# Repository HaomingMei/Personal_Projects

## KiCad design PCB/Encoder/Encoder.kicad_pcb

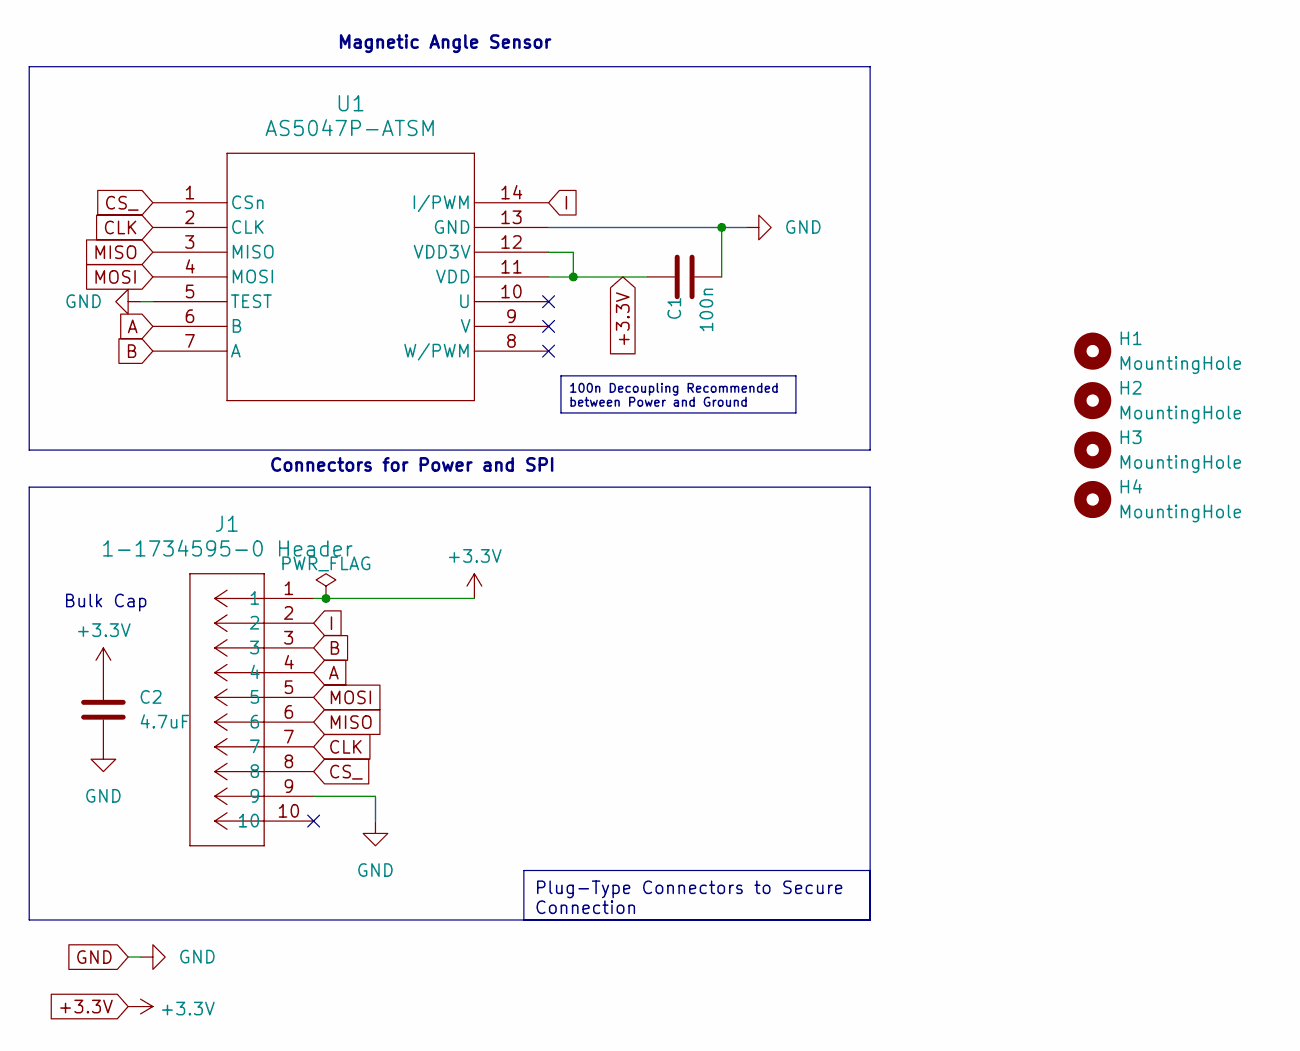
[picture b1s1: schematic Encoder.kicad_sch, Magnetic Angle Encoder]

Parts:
C1: 100n; C_0805_2012Metric
C2: 4.7uF; C_0805_2012Metric
H1, H2, H3, H4: MountingHole; MountingHole_3.2mm_M3
J1: 1-1734595-0 Header; CON10_1X10_DUM_HPI_TYC
U1: AS5047P-ATSM; TSSOP14_OSM

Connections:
+3.3V: C1.1, C2.1, J1.1, U1.11 (VDD), U1.12 (VDD3V)
A: J1.4, U1.6 (B)
B: J1.3, U1.7 (A)
CLK: J1.7, U1.2 (CLK)
CS_: J1.8, U1.1 (CSn)
GND: C1.2, C2.2, J1.9, U1.5 (TEST), U1.13 (GND)
I: J1.2, U1.14 (I/PWM)
MISO: J1.6, U1.3 (MISO)
MOSI: J1.5, U1.4 (MOSI)

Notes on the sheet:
100n Decoupling Recommended between Power and Ground
Plug-Type Connectors to Secure Connection
Bulk Cap
Magnetic Angle Sensor
Connectors for Power and SPI

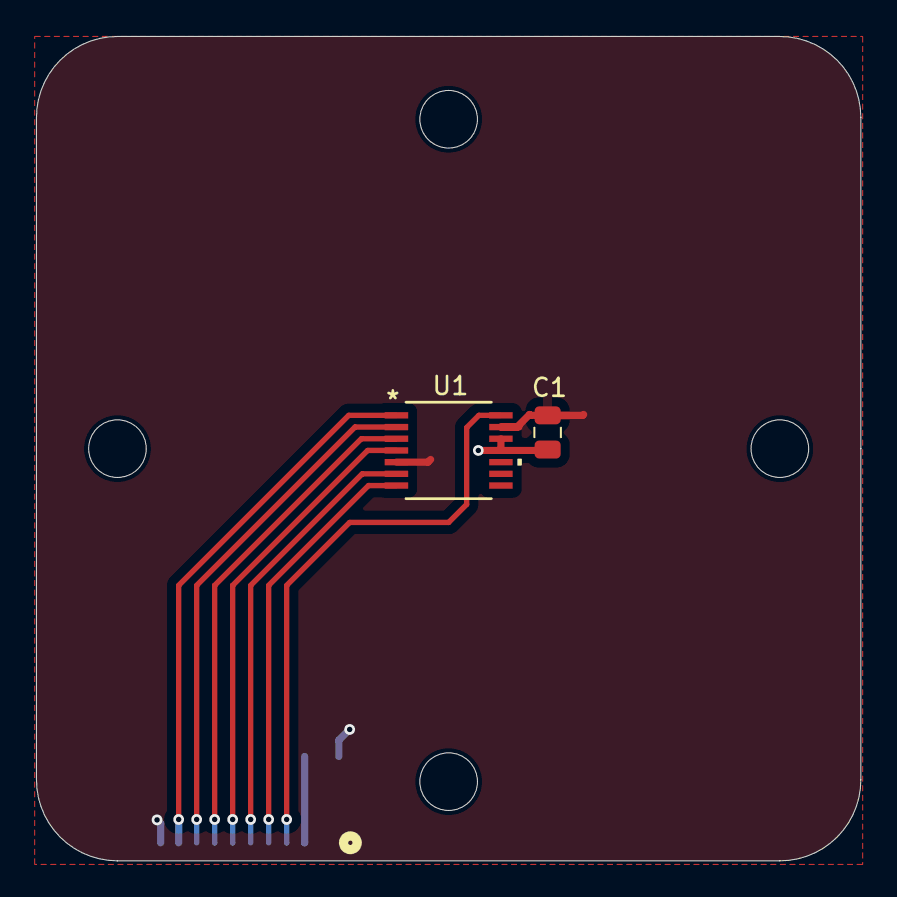
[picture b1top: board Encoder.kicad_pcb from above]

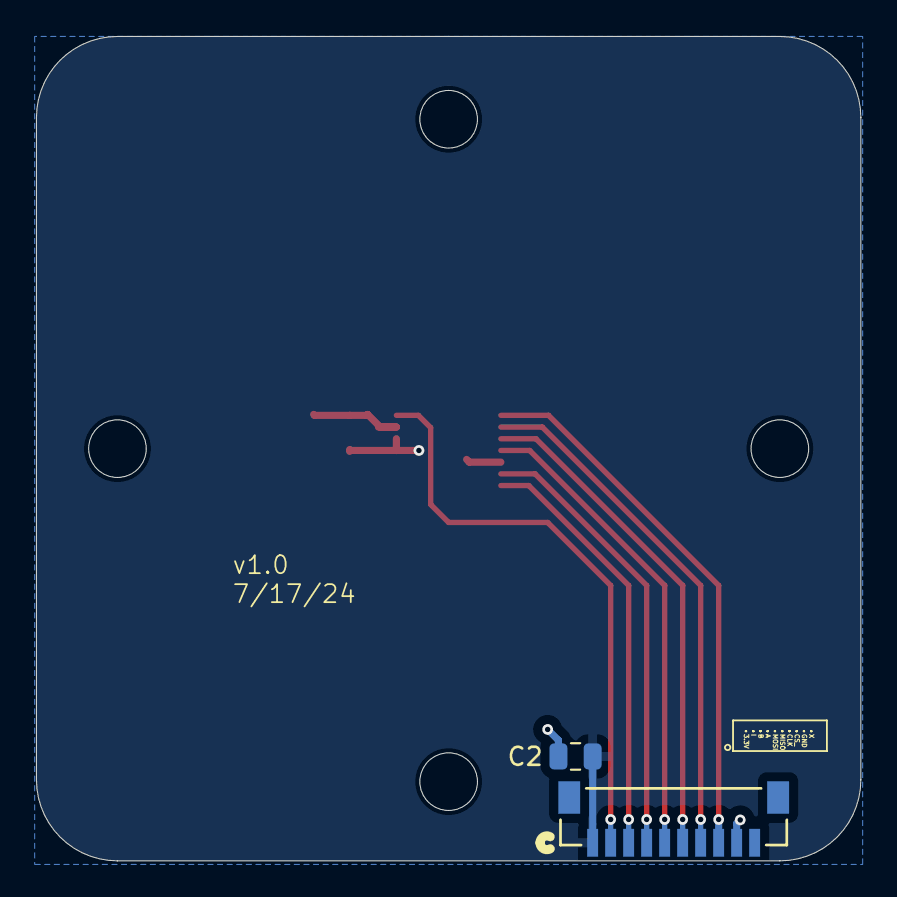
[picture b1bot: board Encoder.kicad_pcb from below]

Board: 2 copper layers, 45.8 x 45.8 mm, 8 parts (2 on the bottom side), 9 nets.

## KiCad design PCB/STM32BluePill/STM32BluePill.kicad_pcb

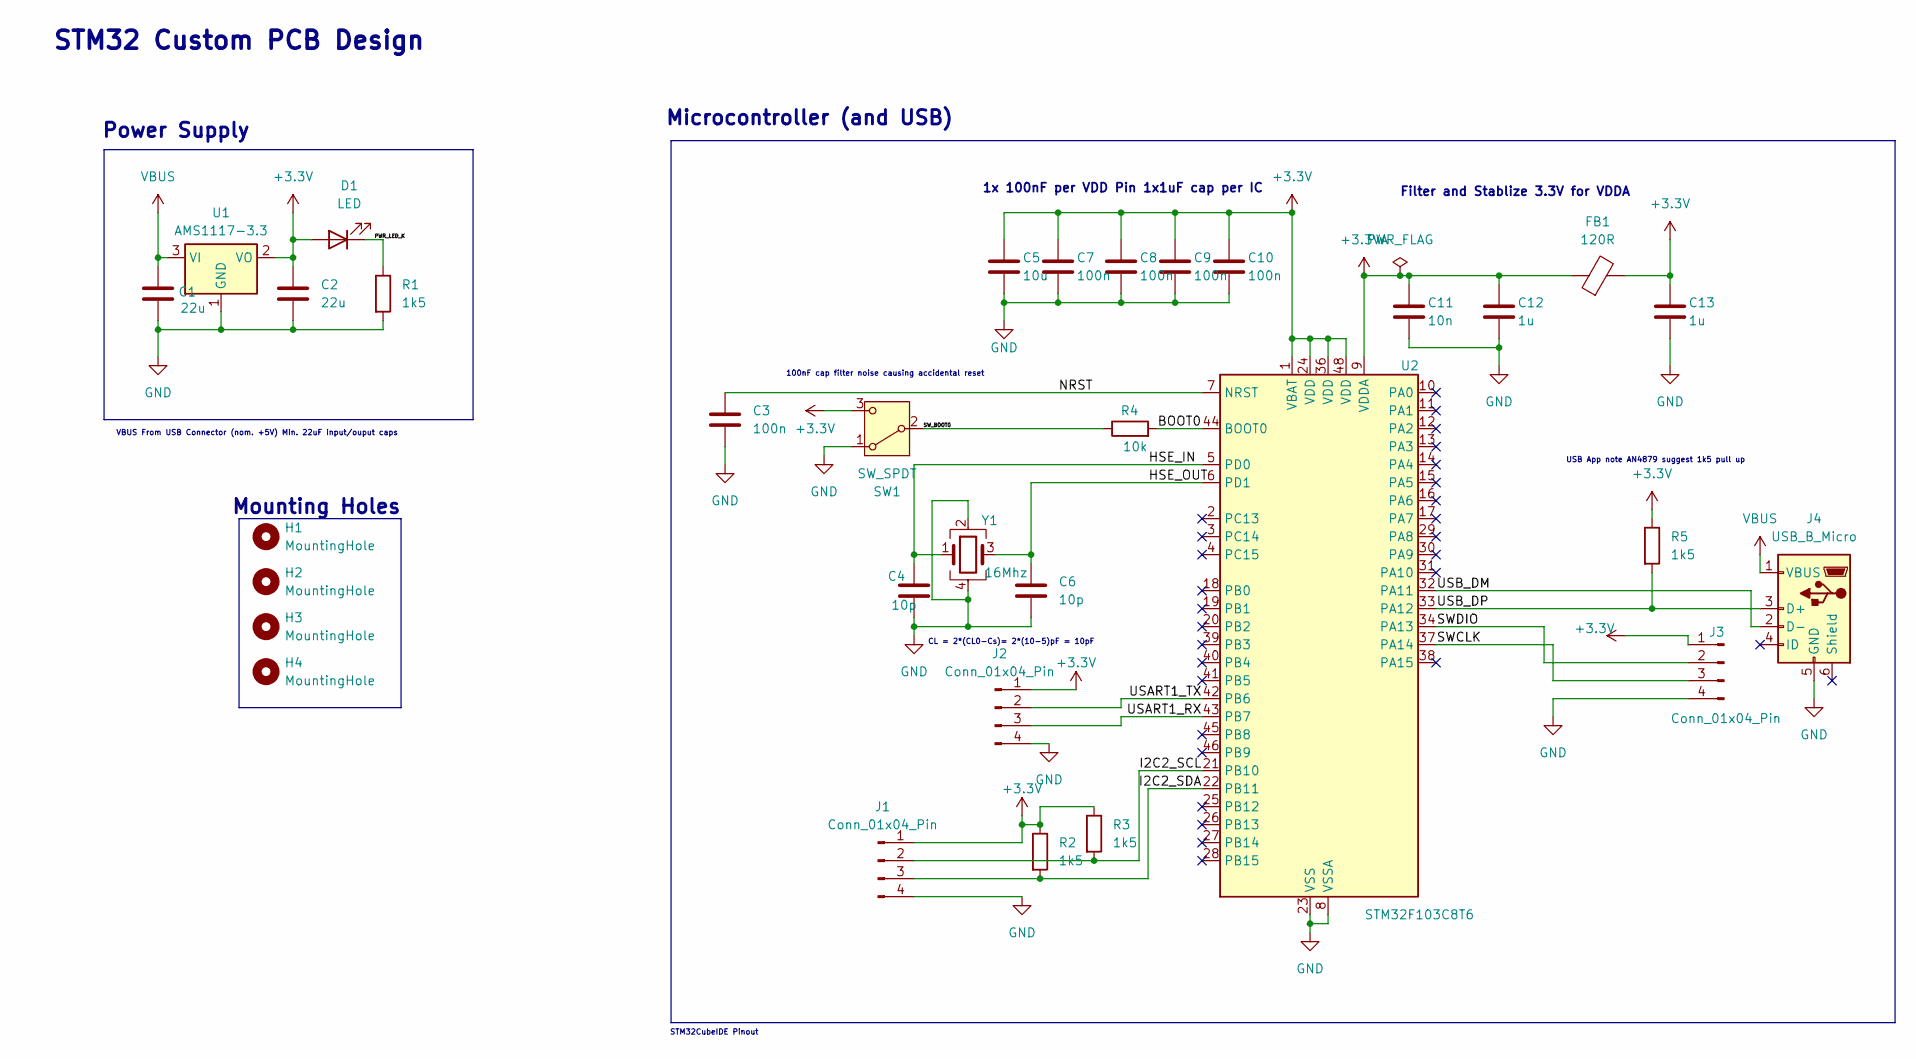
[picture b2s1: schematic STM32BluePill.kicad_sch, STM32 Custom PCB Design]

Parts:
C1, C2: 22u; C_0805_2012Metric
C3, C7, C8, C9, C10: 100n; C_0402_1005Metric
C4, C6: 10p; C_0402_1005Metric
C5: 10u; C_0603_1608Metric
C11: 10n; C_0402_1005Metric
C12, C13: 1u; C_0402_1005Metric
D1: LED; LED_0603_1608Metric
FB1: 120R; L_0603_1608Metric
H1, H2, H3, H4: MountingHole; MountingHole_2.2mm_M2
J1, J2, J3: Conn_01x04_Pin; PinHeader_1x04_P2.54mm_Vertical
J4: USB_B_Micro; USB_Micro-B_Wuerth_629105150521
R1, R2, R3, R5: 1k5; R_0402_1005Metric
R4: 10k; R_0402_1005Metric
SW1: SW_SPDT; SW_SPDT_PCM12
U1: AMS1117-3.3; SOT-223-3_TabPin2
U2: STM32F103C8T6; LQFP-48_7x7mm_P0.5mm
Y1: 16Mhz; Crystal_SMD_3225-4Pin_3.2x2.5mm

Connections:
+3.3V: C2.1, C5.1, C7.1, C8.1, C9.1, C10.1, C13.1, D1.2 (A), FB1.2, J1.1, J2.1, J3.1, R2.1, R3.1, R5.1, SW1.3 (C), U1.2 (VO), U2.1 (VBAT), U2.24 (VDD), U2.36 (VDD), U2.48 (VDD)
+3.3VA: C11.1, C12.1, FB1.1, U2.9 (VDDA)
/BOOT0: R4.2, U2.44 (BOOT0)
/HSE_IN: C4.1, U2.5 (PD0), Y1.1
/HSE_OUT: C6.1, U2.6 (PD1), Y1.3
/I2C2_SCL: J1.2, R3.2, U2.21 (PB10)
/I2C2_SDA: J1.3, R2.2, U2.22 (PB11)
/NRST: C3.1, U2.7 (NRST)
/PWR_LED_K: D1.1 (K), R1.1
/SWCLK: J3.3, U2.37 (PA14)
/SWDIO: J3.2, U2.34 (PA13)
/SW_BOOT0: R4.1, SW1.2 (B)
/USART1_RX: J2.3, U2.43 (PB7)
/USART1_TX: J2.2, U2.42 (PB6)
/USB_DM: J4.2 (D-), U2.32 (PA11)
/USB_DP: J4.3 (D+), R5.2, U2.33 (PA12)
GND: C1.2, C2.2, C3.2, C4.2, C5.2, C6.2, C7.2, C8.2, C9.2, C10.2, C11.2, C12.2, C13.2, J1.4, J2.4, J3.4, J4.5 (GND), R1.2, SW1.1 (A), U1.1 (GND), U2.8 (VSSA), U2.23 (VSS), U2.35 (VSS), U2.47 (VSS), Y1.2, Y1.4
VBUS: C1.1, J4.1 (VBUS), U1.3 (VI)

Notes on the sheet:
Mounting Holes
Power Supply
Filter and Stablize 3.3V for VDDA
USB App note AN4879 suggest 1k5 pull up
100nF cap filter noise causing accidental reset
STM32CubeIDE Pinout
CL = 2*(CL0-Cs)= 2*(10-5)pF = 10pF
STM32 Custom PCB Design
VBUS From USB Connector (nom. +5V) Min. 22uF input/ouput caps
1x 100nF per VDD Pin 1x1uF cap per IC
Microcontroller (and USB)

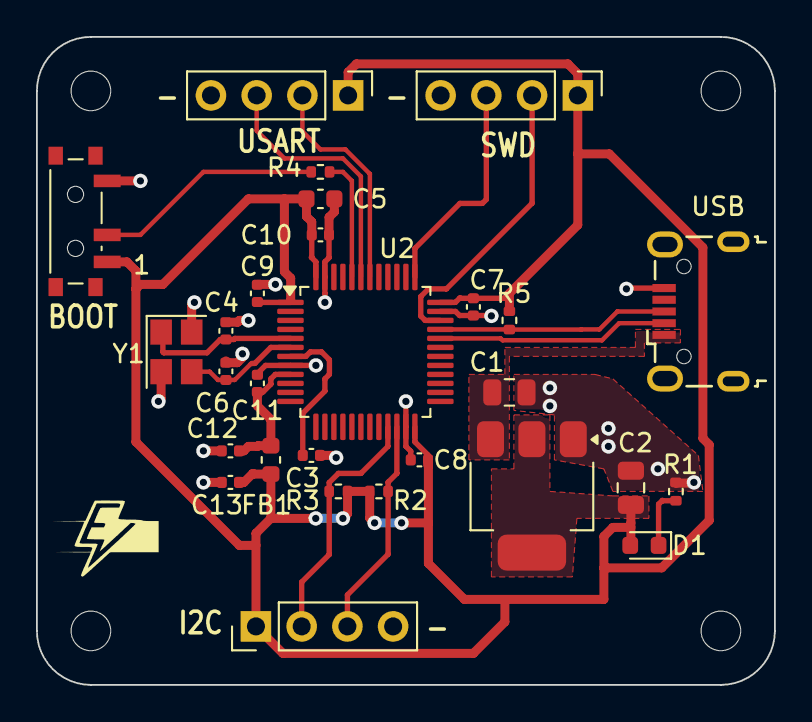
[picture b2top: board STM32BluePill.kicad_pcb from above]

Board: 2 copper layers, 41.0 x 36.0 mm, 32 parts (0 on the bottom side), 18 nets.

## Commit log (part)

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2023-06-22 Dynamic Motor Control Project latest update
2023-08-17 Projects Updated
2023-08-17 Project Updated
2024-07-11 Putting Embedded Projects in Embedded Folder
2024-07-11 Adding BluePill PCB
2024-07-11 Encoder v0.1 LVDS
2024-07-11 Updated Schematics and PCB
2024-07-15 Fixed GroundDetch not grounded
2024-07-15 Fixed Net-, grounded it
2024-07-17 Connectors wrong side fixed, PCB v1.0 Done
2024-08-28 Adding STLINKV3 Adapter and Artificial Intelligence Project Folder Start
2025-06-01 Update 2
2025-06-07 [2970] [Time Beats: 10.00%] [Memory Beats: 90.00%] - LeetPush
2025-06-10 test
2025-06-10 test?
2025-06-10 Updated gitignore
2025-06-10 Try cmsis
2025-06-10 next
2025-06-10 gitignore update
2025-06-10 Moved gitignore to root
2025-06-10 Changed gitignore
2025-06-10 rest
2025-06-10 fixed gitignore
2025-06-10 testa
2025-06-10 last
2025-06-10 SDRAM Starting address added
2025-06-11 [290] [Time Beats: 0.50%] [Memory Beats: 89.69%] - LeetPush
2025-06-15 [1525] [Time Beats: 100.00%] [Memory Beats: 57.00%] - LeetPush
2025-06-20 Memory Protection Unit First Draft Untested
2025-06-21 Updating
2025-06-21 [217] [Time Beats: 10.93%] [Memory Beats: 100.00%] - LeetPush
2025-06-21 [242] [Time Beats: 100.00%] [Memory Beats: 100.00%] - LeetPush
2025-06-21 [1] [Time Beats: 44.00%] [Memory Beats: 99.98%] - LeetPush
2025-06-21 [49] [Time Beats: 20.82%] [Memory Beats: 99.96%] - LeetPush
2025-06-21 [347] [Time Beats: 10.00%] [Memory Beats: 100.00%] - LeetPush
2025-06-21 [238] [Time Beats: 6.09%] [Memory Beats: 100.00%] - LeetPush
2025-06-21 [36] [Time Beats: 11.90%] [Memory Beats: 100.00%] - LeetPush
2025-06-21 [125] [Time Beats: 38.69%] [Memory Beats: 100.00%] - LeetPush
2025-06-21 [167] [Time Beats: 2.48%] [Memory Beats: 100.00%] - LeetPush
2025-06-21 [15] [Time Beats: 21.26%] [Memory Beats: 100.00%] - LeetPush
2025-06-21 [11] [Time Beats: 5.69%] [Memory Beats: 99.94%] - LeetPush
2025-06-21 [42] [Time Beats: 5.21%] [Memory Beats: 100.00%] - LeetPush
2025-06-21 [84] [Time Beats: 5.04%] [Memory Beats: 100.00%] - LeetPush
2025-06-21 [853] [Time Beats: 7.08%] [Memory Beats: 92.19%] - LeetPush
2025-06-21 [739] [Time Beats: 5.01%] [Memory Beats: 21.50%] - LeetPush
2025-06-21 [22] [Time Beats: 36.99%] [Memory Beats: 72.09%] - LeetPush
2025-06-21 [150] [Time Beats: 7.10%] [Memory Beats: 100.00%] - LeetPush
2025-06-21 [155] [Time Beats: 5.13%] [Memory Beats: 100.00%] - LeetPush
2025-06-21 [704] [Time Beats: 0.83%] [Memory Beats: 99.97%] - LeetPush
2025-06-21 [74] [Time Beats: 100.00%] [Memory Beats: 100.00%] - LeetPush
2025-06-21 [875] [Time Beats: 5.19%] [Memory Beats: 100.00%] - LeetPush
2025-06-21 [153] [Time Beats: 100.00%] [Memory Beats: 100.00%] - LeetPush
2025-06-21 [33] [Time Beats: 2.47%] [Memory Beats: 100.00%] - LeetPush
2025-06-21 [981] [Time Beats: 5.12%] [Memory Beats: 99.91%] - LeetPush
2025-06-21 [4] [Time Beats: 5.63%] [Memory Beats: 99.95%] - LeetPush
2025-06-21 [121] [Time Beats: 5.07%] [Memory Beats: 99.99%] - LeetPush
2025-06-21 [3] [Time Beats: 21.95%] [Memory Beats: 89.09%] - LeetPush
2025-06-21 [424] [Time Beats: 63.70%] [Memory Beats: 100.00%] - LeetPush
2025-06-21 [567] [Time Beats: 46.44%] [Memory Beats: 100.00%] - LeetPush
2025-06-21 [76] [Time Beats: 9.69%] [Memory Beats: 5.06%] - LeetPush
2025-06-21 [206] [Time Beats: 2.24%] [Memory Beats: 99.99%] - LeetPush
2025-06-21 [21] [Time Beats: 4.20%] [Memory Beats: 99.95%] - LeetPush
2025-06-21 [143] [Time Beats: 7.71%] [Memory Beats: 100.00%] - LeetPush
2025-06-21 [226] [Time Beats: 0.09%] [Memory Beats: 100.00%] - LeetPush
2025-06-21 [104] [Time Beats: 0.51%] [Memory Beats: 75.30%] - LeetPush
2025-06-21 Updated the LCD_Init functions, complete LTDC's PPL CLK Configuration
2025-06-25 Added PLL DSI (clock) and HLDC_dsi handle
2025-06-25 Adding new drivers file
2025-06-25 Added otm8009a (display driver files) and partially completely Setting up CMD and LPCmd
2025-06-25 Finished CmdConfig
2025-06-25 Finished Setting up LPCmd. Allow short read/write in low-power, but high-speed for long/max read/write
2025-06-28 OTM IO, Object, and Physical DSI Timing Update
2025-06-29 Starting the keypad implementation.
2025-06-30 Added GPIOs for Keypad
2025-06-30 Updated GPIO Labels
2025-07-04 Updated Keypad.h for scan algo
2025-07-04 Fixed Some Error
2025-07-04 Updated h file to keep track of port and pin number
2025-07-05 Updated Code to extract Row and Column Pin information: port, pin(one-hot-encoded), and pin number
2025-07-05 Updated Restore_Rows Function
2025-07-05 Finished Keypad Drivers (Draft 1), UnTested
2025-07-05 [539] [Time Beats: 100.00%] [Memory Beats: 55.69%] - LeetPush
2025-07-05 [693] [Time Beats: 100.00%] [Memory Beats: 11.40%] - LeetPush
2025-07-06 [143] [Time Beats: 100.00%] [Memory Beats: 33.96%] - LeetPush
2025-07-09 Update ioc
2025-07-09 Some Tweaks, Finish Code for Bluetooth Processing
2025-07-10 Small Outline. Planning to Use Ring Buffer. Going to Program Simple Implementation Until RTOS system is ready
2025-07-12 Redoing Problem. Wipe
2025-07-12 Deleted
2025-07-12 [539] [Time Beats: 100.00%] [Memory Beats: 76.02%] - LeetPush
2025-07-13 [26] [Time Beats: 15.91%] [Memory Beats: 20.60%] - LeetPush
2025-07-14 [26] [Time Beats: 100.00%] [Memory Beats: 78.71%] - LeetPush
2025-07-14 [290] [Time Beats: 100.00%] [Memory Beats: 68.82%] - LeetPush
2025-07-14 [2193] [Time Beats: 100.00%] [Memory Beats: 63.70%] - LeetPush
2025-07-15 [820] [Time Beats: 7.44%] [Memory Beats: 99.17%] - LeetPush
2025-07-15 [1700] [Time Beats: 100.00%] [Memory Beats: 41.44%] - LeetPush
2025-07-16 Ring Buffer 127 bytes of space available ok. Write the HC05 Functions Next
2025-07-23 [225] [Time Beats: 100.00%] [Memory Beats: 99.16%] - LeetPush
2025-07-23 [933] [Time Beats: 5.01%] [Memory Beats: 5.04%] - LeetPush
2025-07-23 [933] [Time Beats: 5.55%] [Memory Beats: 5.04%] - LeetPush
2025-07-23 Removig cause glitched
2025-07-23 [933] [Time Beats: 82.08%] [Memory Beats: 35.92%] - LeetPush
2025-07-23 [933] [Time Beats: 86.35%] [Memory Beats: 35.92%] - LeetPush
2025-07-26 Practicing Timer Triggered ADC Conversion -> DMA Transfer
2025-07-27 [83] [Time Beats: 100.00%] [Memory Beats: 36.94%] - LeetPush
2025-07-27 [876] [Time Beats: 100.00%] [Memory Beats: 25.49%] - LeetPush
2025-07-27 [141] [Time Beats: 97.33%] [Memory Beats: 53.28%] - LeetPush
2025-07-27 [237] [Time Beats: 95.03%] [Memory Beats: 53.88%] - LeetPush
2025-07-29 [101] [Time Beats: 100.00%] [Memory Beats: 61.09%] - LeetPush
2025-07-29 [1046] [Time Beats: 100.00%] [Memory Beats: 96.69%] - LeetPush
2025-07-30 [506] [Time Beats: 86.15%] [Memory Beats: 55.96%] - LeetPush
2025-07-30 [703] [Time Beats: 83.16%] [Memory Beats: 61.53%] - LeetPush
2025-08-01 [203] [Time Beats: 100.00%] [Memory Beats: 99.65%] - LeetPush
2025-08-02 [232] [Time Beats: 100.00%] [Memory Beats: 26.72%] - LeetPush
2025-08-03 [451] [Time Beats: 54.53%] [Memory Beats: 15.11%] - LeetPush
2025-08-04 [496] [Time Beats: 42.46%] [Memory Beats: 15.09%] - LeetPush
2025-08-04 [496] [Time Beats: 100.00%] [Memory Beats: 15.09%] - LeetPush
2025-08-07 [496] [Time Beats: 11.41%] [Memory Beats: 96.58%] - LeetPush
2025-08-10 [145] [Time Beats: 100.00%] [Memory Beats: 14.63%] - LeetPush
2025-08-10 [145] [Time Beats: 100.00%] [Memory Beats: 71.51%] - LeetPush
2025-08-10 [94] [Time Beats: 100.00%] [Memory Beats: 63.15%] - LeetPush
2025-08-10 [144] [Time Beats: 100.00%] [Memory Beats: 40.07%] - LeetPush
2025-08-10 [19] [Time Beats: 0.66%] [Memory Beats: 59.14%] - LeetPush
2025-08-10 [19] [Time Beats: 100.00%] [Memory Beats: 59.14%] - LeetPush
2025-08-12 [543] [Time Beats: 100.00%] [Memory Beats: 42.38%] - LeetPush
2025-08-13 [496] [Time Beats: 100.00%] [Memory Beats: 15.21%] - LeetPush
2025-08-14 [94] [Time Beats: 100.00%] [Memory Beats: 86.75%] - LeetPush
2025-08-14 [145] [Time Beats: 100.00%] [Memory Beats: 99.90%] - LeetPush
2025-08-14 [144] [Time Beats: 100.00%] [Memory Beats: 92.86%] - LeetPush
2025-08-14 [543] [Time Beats: 100.00%] [Memory Beats: 92.62%] - LeetPush
2025-08-14 [110] [Time Beats: 100.00%] [Memory Beats: 83.83%] - LeetPush
2025-08-14 [100] [Time Beats: 100.00%] [Memory Beats: 47.96%] - LeetPush
2025-08-16 [1448] [Time Beats: 87.44%] [Memory Beats: 26.95%] - LeetPush
2025-08-16 [1448] [Time Beats: 93.62%] [Memory Beats: 61.74%] - LeetPush
2025-08-16 Remove
2025-08-16 [1448] [Time Beats: 92.37%] [Memory Beats: 83.34%] - LeetPush
2025-08-18 [98] [Time Beats: 100.00%] [Memory Beats: 17.70%] - LeetPush
2025-08-19 [230] [Time Beats: 100.00%] [Memory Beats: 17.71%] - LeetPush
2025-08-19 [102] [Time Beats: 100.00%] [Memory Beats: 89.06%] - LeetPush
2025-08-19 [572] [Time Beats: 100.00%] [Memory Beats: 7.81%] - LeetPush
2025-08-20 [138] [Time Beats: 28.50%] [Memory Beats: 84.83%] - LeetPush
2025-08-20 [138] [Time Beats: 65.27%] [Memory Beats: 45.16%] - LeetPush
2025-08-20 [2] [Time Beats: 7.38%] [Memory Beats: 44.19%] - LeetPush
2025-08-20 [2] [Time Beats: 39.25%] [Memory Beats: 44.19%] - LeetPush
2025-08-21 [146] [Time Beats: 94.44%] [Memory Beats: 82.35%] - LeetPush
2025-08-21 [235] [Time Beats: 60.84%] [Memory Beats: 64.56%] - LeetPush
2025-08-21 [235] [Time Beats: 96.43%] [Memory Beats: 64.56%] - LeetPush
2025-08-21 [199] [Time Beats: 100.00%] [Memory Beats: 40.18%] - LeetPush
2025-08-23 [136] [Time Beats: 100.00%] [Memory Beats: 58.01%] - LeetPush
2025-08-24 [191] [Time Beats: 100.00%] [Memory Beats: 12.24%] - LeetPush
2025-08-24 [191] [Time Beats: 100.00%] [Memory Beats: 80.57%] - LeetPush
2025-08-24 [338] [Time Beats: 26.17%] [Memory Beats: 9.22%] - LeetPush
2025-08-24 [338] [Time Beats: 26.17%] [Memory Beats: 35.71%] - LeetPush
2025-08-24 [338] [Time Beats: 100.00%] [Memory Beats: 57.94%] - LeetPush
2025-08-24 [190] [Time Beats: 100.00%] [Memory Beats: 27.45%] - LeetPush
2025-08-24 [268] [Time Beats: 100.00%] [Memory Beats: 70.15%] - LeetPush
2025-08-27 [746] [Time Beats: 100.00%] [Memory Beats: 75.22%] - LeetPush
2025-08-28 [78] [Time Beats: 100.00%] [Memory Beats: 80.85%] - LeetPush
2025-08-28 [90] [Time Beats: 100.00%] [Memory Beats: 66.75%] - LeetPush
2025-08-28 [39] [Time Beats: 100.00%] [Memory Beats: 72.75%] - LeetPush
2025-08-28 [40] [Time Beats: 100.00%] [Memory Beats: 60.73%] - LeetPush
2025-08-29 [46] [Time Beats: 6.04%] [Memory Beats: 5.17%] - LeetPush
2025-08-30 [79] [Time Beats: 8.98%] [Memory Beats: 16.89%] - LeetPush
2025-08-31 [131] [Time Beats: 61.80%] [Memory Beats: 61.12%] - LeetPush
2025-09-05 Removing cause we practicing
2025-09-05 [78] [Time Beats: 100.00%] [Memory Beats: 60.10%] - LeetPush
2025-09-06 [90] [Time Beats: 100.00%] [Memory Beats: 49.45%] - LeetPush
2025-09-06 [39] [Time Beats: 100.00%] [Memory Beats: 90.70%] - LeetPush
2025-09-12 [40] [Time Beats: 100.00%] [Memory Beats: 82.69%] - LeetPush
2025-09-13 [131] [Time Beats: 59.20%] [Memory Beats: 60.73%] - LeetPush
2025-09-14 [79] [Time Beats: 9.13%] [Memory Beats: 34.02%] - LeetPush
2025-09-15 [79] [Time Beats: 100.00%] [Memory Beats: 16.65%] - LeetPush
2025-09-17 [1] [Time Beats: 100.00%] [Memory Beats: 36.04%] - LeetPush
2025-09-17 [242] [Time Beats: 100.00%] [Memory Beats: 11.49%] - LeetPush
2025-09-17 [242] [Time Beats: 100.00%] [Memory Beats: 48.47%] - LeetPush
2025-09-17 [217] [Time Beats: 56.92%] [Memory Beats: 46.46%] - LeetPush
2025-09-17 [49] [Time Beats: 25.35%] [Memory Beats: 15.75%] - LeetPush
2025-09-17 bugged
2025-09-17 [49] [Time Beats: 10.97%] [Memory Beats: 10.64%] - LeetPush
2025-09-17 [347] [Time Beats: 100.00%] [Memory Beats: 28.08%] - LeetPush
2025-09-20 [94] [Time Beats: 100.00%] [Memory Beats: 32.03%] - LeetPush
2025-09-20 [145] [Time Beats: 100.00%] [Memory Beats: 99.73%] - LeetPush
2025-09-20 [102] [Time Beats: 100.00%] [Memory Beats: 88.83%] - LeetPush
2025-09-27 [133] [Time Beats: 35.93%] [Memory Beats: 77.65%] - LeetPush
2025-09-27 [133] [Time Beats: 100.00%] [Memory Beats: 77.65%] - LeetPush
2025-09-27 [1] [Time Beats: 100.00%] [Memory Beats: 50.73%] - LeetPush
2025-09-27 [49] [Time Beats: 84.38%] [Memory Beats: 65.98%] - LeetPush
2025-12-29 [49] [Time Beats: 51.09%] [Memory Beats: 64.46%] - LeetPush
2025-12-29 Pushing
2025-12-29 [14] [Time Beats: 5.08%] [Memory Beats: 5.01%] - LeetPush
2026-01-18 need to add process and plot
